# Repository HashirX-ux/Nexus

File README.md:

# Nexus

> A wireless 3x4 macropad i'm building to speed up my workflow. Hot-swap switches, per-key RGB, an OLED screen for status, and a rotary encoder for macros. Works wired or wireless.

---

## What is it?

Nexus is a custom 3x4 (12 key) macropad i designed mainly for shortcuts and repetitive commands i was tired of typing out. Built around a nice!nano v2 so it can do bluetooth LE, with USB-C as a backup if the battery dies or i just don't feel like pairing it again. 12 hot swap sockets, per key RGB underneath, an EC11 rotary encoder, and a little OLED that shows battery % and what its connected to.

(quick note to future me: the tagline used to say QMK somewhere, thats wrong, QMK doesnt really do BLE on this board properly so i switched to ZMK. fix that if you see it anywhere else)

## Why build it

Because reaching over to a full keyboard just to hit a macro or shortcut combo got annoying. If i build the layout, lighting and firmware myself it actually fits how i work instead of some generic layout someone else made.

---

## Status

Research + design phase mostly done, now just cleaning stuff up. Schematic and routing still need some touch ups here and there. Full build log with all the component reasoning is in [journal.md](./journal.md) if you wanna see why i picked what i picked (spoiler: half of it was just "this was in stock on lcsc").

- [x] Component research (MCU, diodes, switches, USB-C, passives)
- [x] Schematic design
- [x] PCB routing
- [x] PCB fabrication
- [x] Firmware pin mapping
- [x] Assembly
- [x] Case design

---

## Planned Specs

| Component | Choice |
|---|---|
| Layout | 3x4, 12 keys |
| MCU | nice!nano v2 (nRF52840) |
| Connectivity | Bluetooth LE (wireless) + USB-C (wired) |
| Switches | Hot-swap, MX-compatible (Kailh / Gateron / Cherry MX) |
| Matrix diodes | 1N4148 |
| RGB | Per-key, WS2812B |
| Encoder | EC11 rotary encoder |
| Display | OLED - battery % + connected device |
| Firmware | ZMK |
| USB | USB-C, USB 2.0 (480Mbps, 5V/500mA) |

---

```
```

Tried to keep this organized roughly the way hack club's [hardware codex shipping guide](https://codex.hackclub.com/shipping/101/) recommends - source files seperate from the manufacturing stuff so its easier for someone else to just grab and rebuild.

> If you dont wanna open kicad just to look at the board, theres a KiCanvas link so you can view it in browser:
> 

---

## Build log

Most of the actual thinking (datasheets i looked at, why i swapped parts, dumb mistakes i made along the way) is in [journal.md](./journal.md). Genuinely recommend reading it if your building something similar, its more useful than just staring at the BOM.

---

## Roadmap

1. finalize schematic (matrix wiring, rgb data line, oled i2c, encoder pins, reset button)
2. route + order the pcb
3. build/test zmk firmware against actual pin assignments (not just what i think they are)
4. design + print the case
5. assemble, flash, pair, hope it works first try

---

## How to build

### 1. order the PCB

1. go to [JLCPCB](https://jlcpcb.com)
2. upload [`Gerber.zip`](./Gerber.zip)
3. settings: 2 layer, FR-4, 1.6mm, HASL (or ENIG if your feeling fancy)
4. order the parts seperately with [`Nexus-BOM.csv`](./Nexus-BOM.csv) as your shopping list - digikey, lcsc, aliexpress all work fine

### 2. print the case

1. open [`cad/`](./cad) - print the `.stl` as is, or crack open the `.f3d` in fusion if you wanna change dimensions
2. 0.2mm layer height, ~20% infill is plenty, its just sitting on a desk not getting thrown around
3. test fit the plate BEFORE you solder anything, learned that one the hard way

### 3. assemble

1. solder the nice!nano v2 diodes resistors and other supprt parts per the [`pcb/`](./pcb) schematic
2. solder in the hot swap sockets, then just press the switches in, no soldering needed there
3. wire the oled, encoder and rgb chain per the pin notes in [`journal.md`](./journal.md)
4. seat the finished pcb intothe case

### 4. flash it

1. follow the zmk build steps in [`firmware/`](./firmware) (shield config + keymap)
2. double tap reset on the nice!nano to drop into UF2 bootloader mode
3. drag the compiled `.uf2` onto the drive that shows up
4. pair over bluetooth, or just plg it in over usb-c if you want wired

### 5. done

flip it over, look at the rgb for a bit, start binding macros. if somethings broken check [`journal.md`](./journal.md) first, saves time vs trying to figure it out from scratch again.

---

## BOM

ful parts list + links in [`Nexus-BOM.csv`](./Nexus-BOM.csv)

---

## Credits

- [ZMK Firmware](https://zmk.dev/)
- [nice!nano](https://nicekeyboards.com/nice-nano/)
- [nice!nano docs](https://nicekeyboards.com/docs/nice-nano/) - pinout + hardware ref, used this constantly

Built by **Hashir**

---

## License

MIT, see [LICENSE](./LICENSE)

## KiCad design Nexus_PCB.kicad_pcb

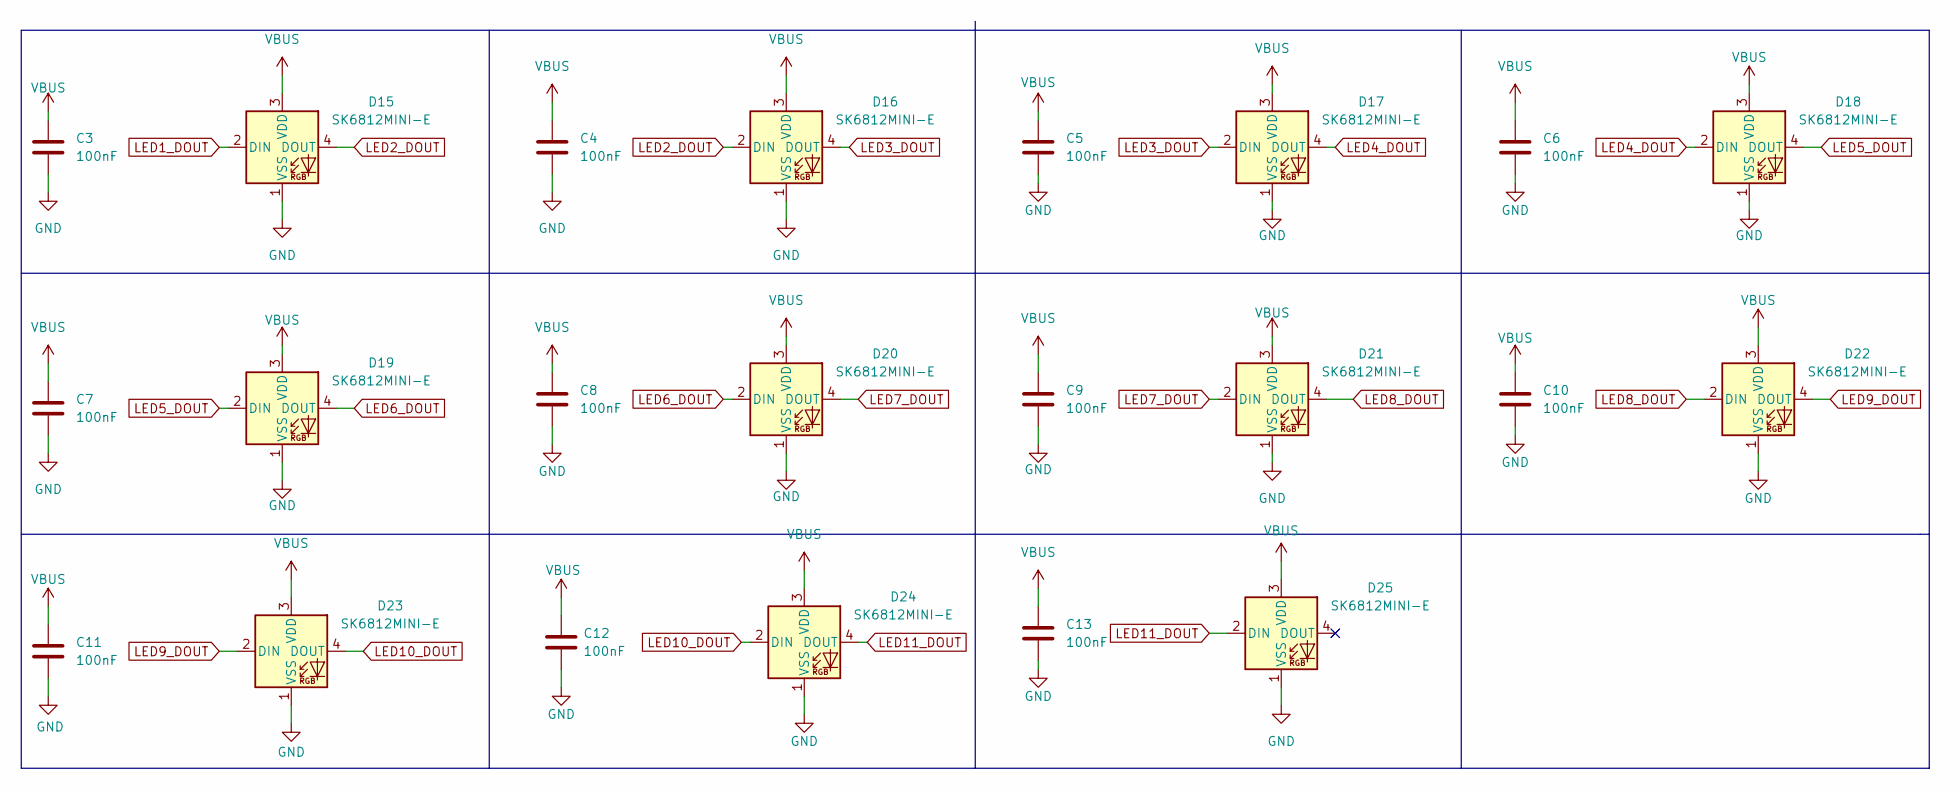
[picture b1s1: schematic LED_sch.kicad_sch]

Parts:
C3, C4, C5, C6, C7, C8, C9, C10, C11, C12, C13: 100nF; C_0805_2012Metric_Pad1.18x1.45mm_HandSolder
D15, D16, D17, D18, D19, D20, D21, D22, D23, D24, D25: SK6812MINI-E; LED_SK6812MINI-E_3.2x2.8mm_P1.5mm_ReverseMount

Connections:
GND: C3.2, C4.2, C5.2, C6.2, C7.2, C8.2, C9.2, C10.2, C11.2, C12.2, C13.2, D15.1 (VSS), D16.1 (VSS), D17.1 (VSS), D18.1 (VSS), D19.1 (VSS), D20.1 (VSS), D21.1 (VSS), D22.1 (VSS), D23.1 (VSS), D24.1 (VSS), D25.1 (VSS); also elsewhere on the board
LED1_DOUT: D15.2 (DIN); also elsewhere on the board
LED2_DOUT: D15.4 (DOUT), D16.2 (DIN)
LED3_DOUT: D16.4 (DOUT), D17.2 (DIN)
LED4_DOUT: D17.4 (DOUT), D18.2 (DIN)
LED5_DOUT: D18.4 (DOUT), D19.2 (DIN)
LED6_DOUT: D19.4 (DOUT), D20.2 (DIN)
LED7_DOUT: D20.4 (DOUT), D21.2 (DIN)
LED8_DOUT: D21.4 (DOUT), D22.2 (DIN)
LED9_DOUT: D22.4 (DOUT), D23.2 (DIN)
LED10_DOUT: D23.4 (DOUT), D24.2 (DIN)
LED11_DOUT: D24.4 (DOUT), D25.2 (DIN)
VBUS: C3.1, C4.1, C5.1, C6.1, C7.1, C8.1, C9.1, C10.1, C11.1, C12.1, C13.1, D15.3 (VDD), D16.3 (VDD), D17.3 (VDD), D18.3 (VDD), D19.3 (VDD), D20.3 (VDD), D21.3 (VDD), D22.3 (VDD), D23.3 (VDD), D24.3 (VDD), D25.3 (VDD); also elsewhere on the board

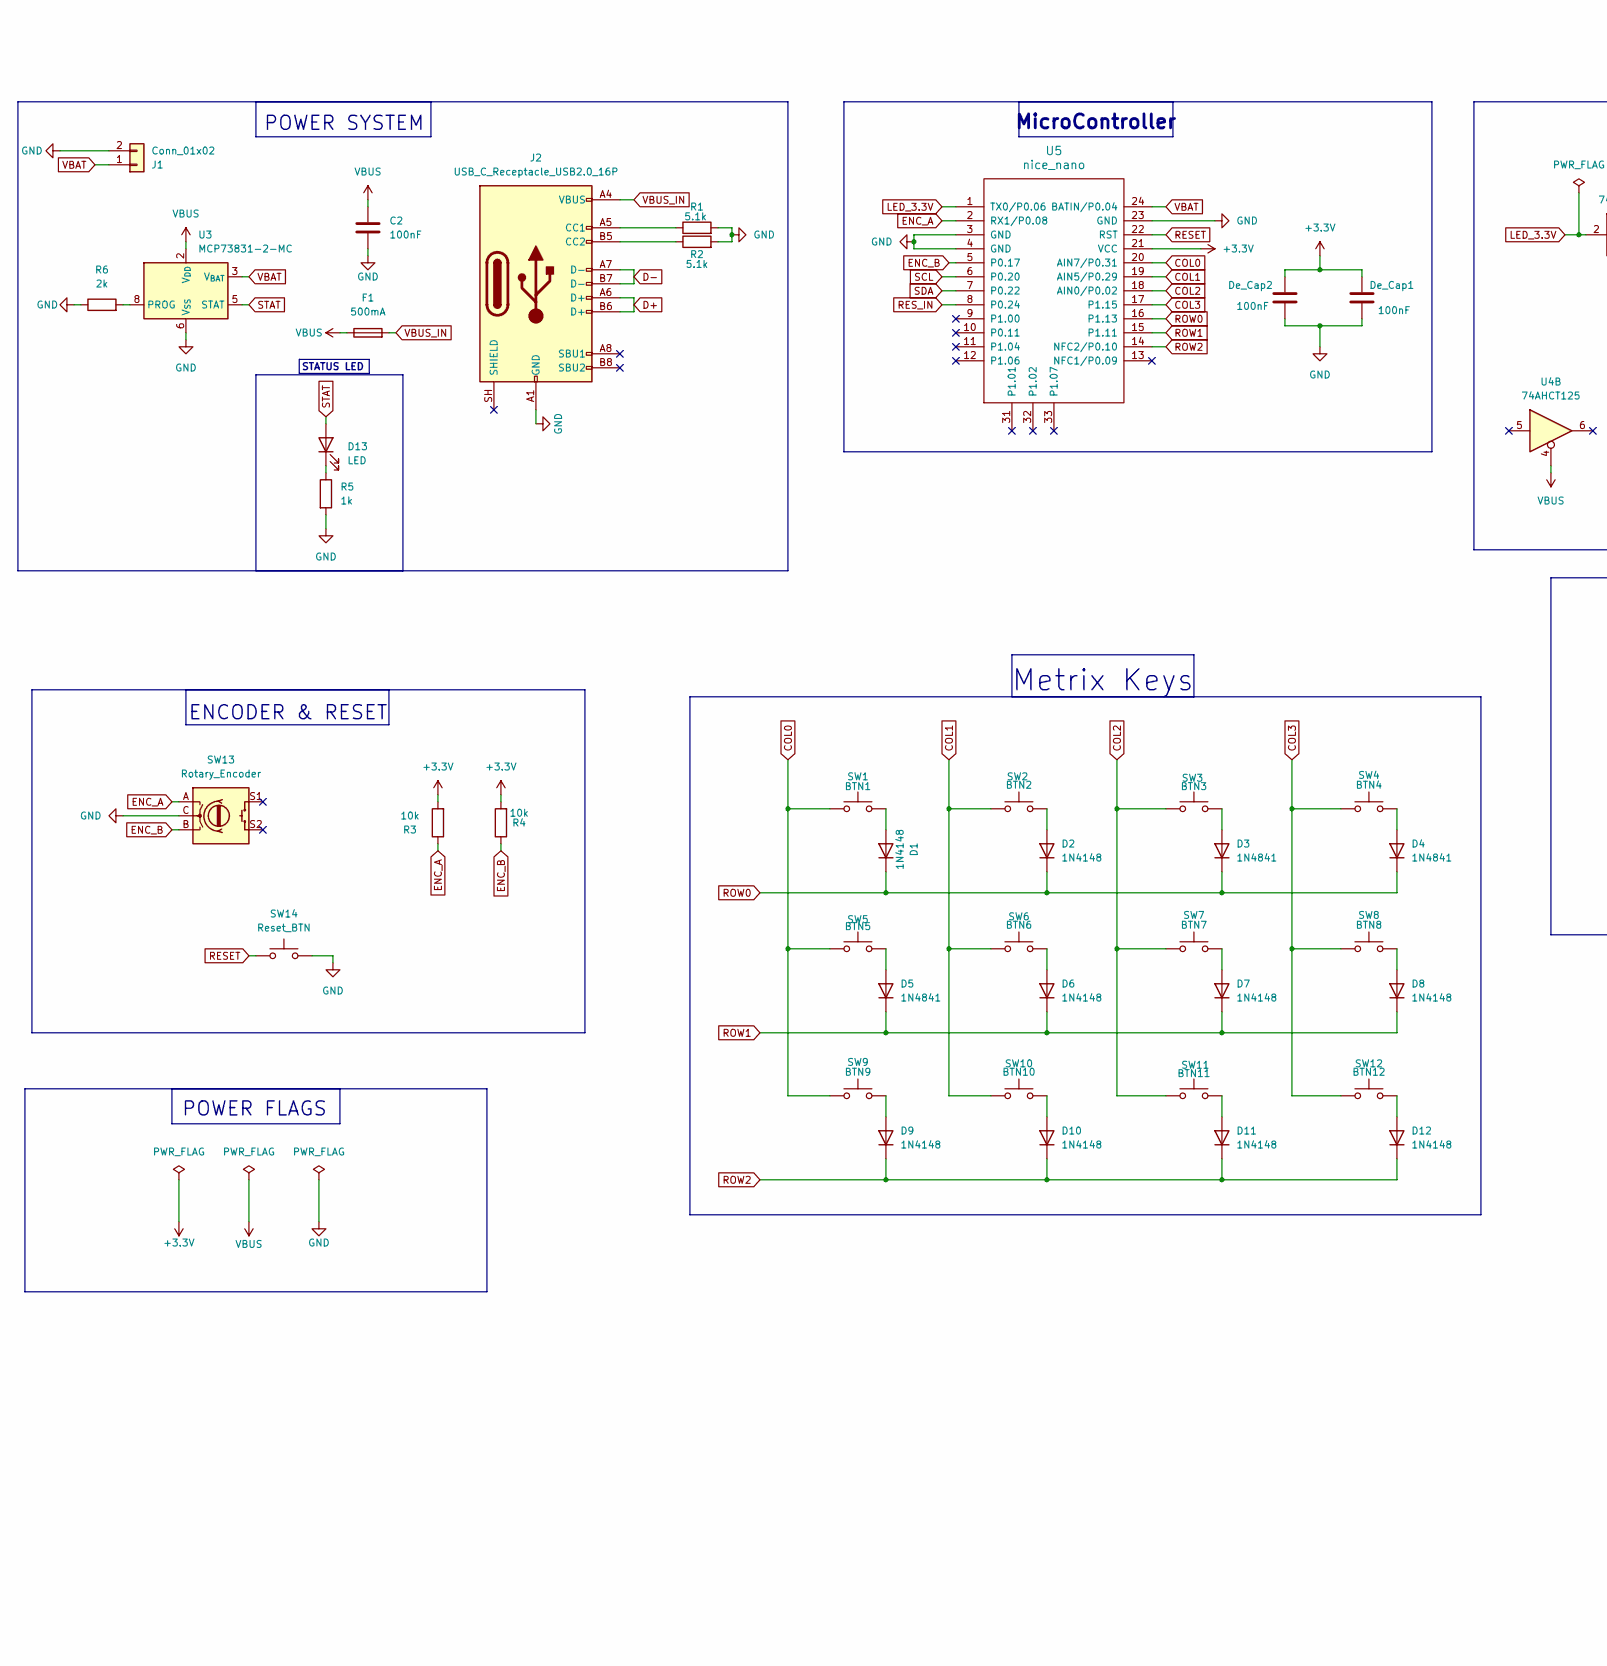
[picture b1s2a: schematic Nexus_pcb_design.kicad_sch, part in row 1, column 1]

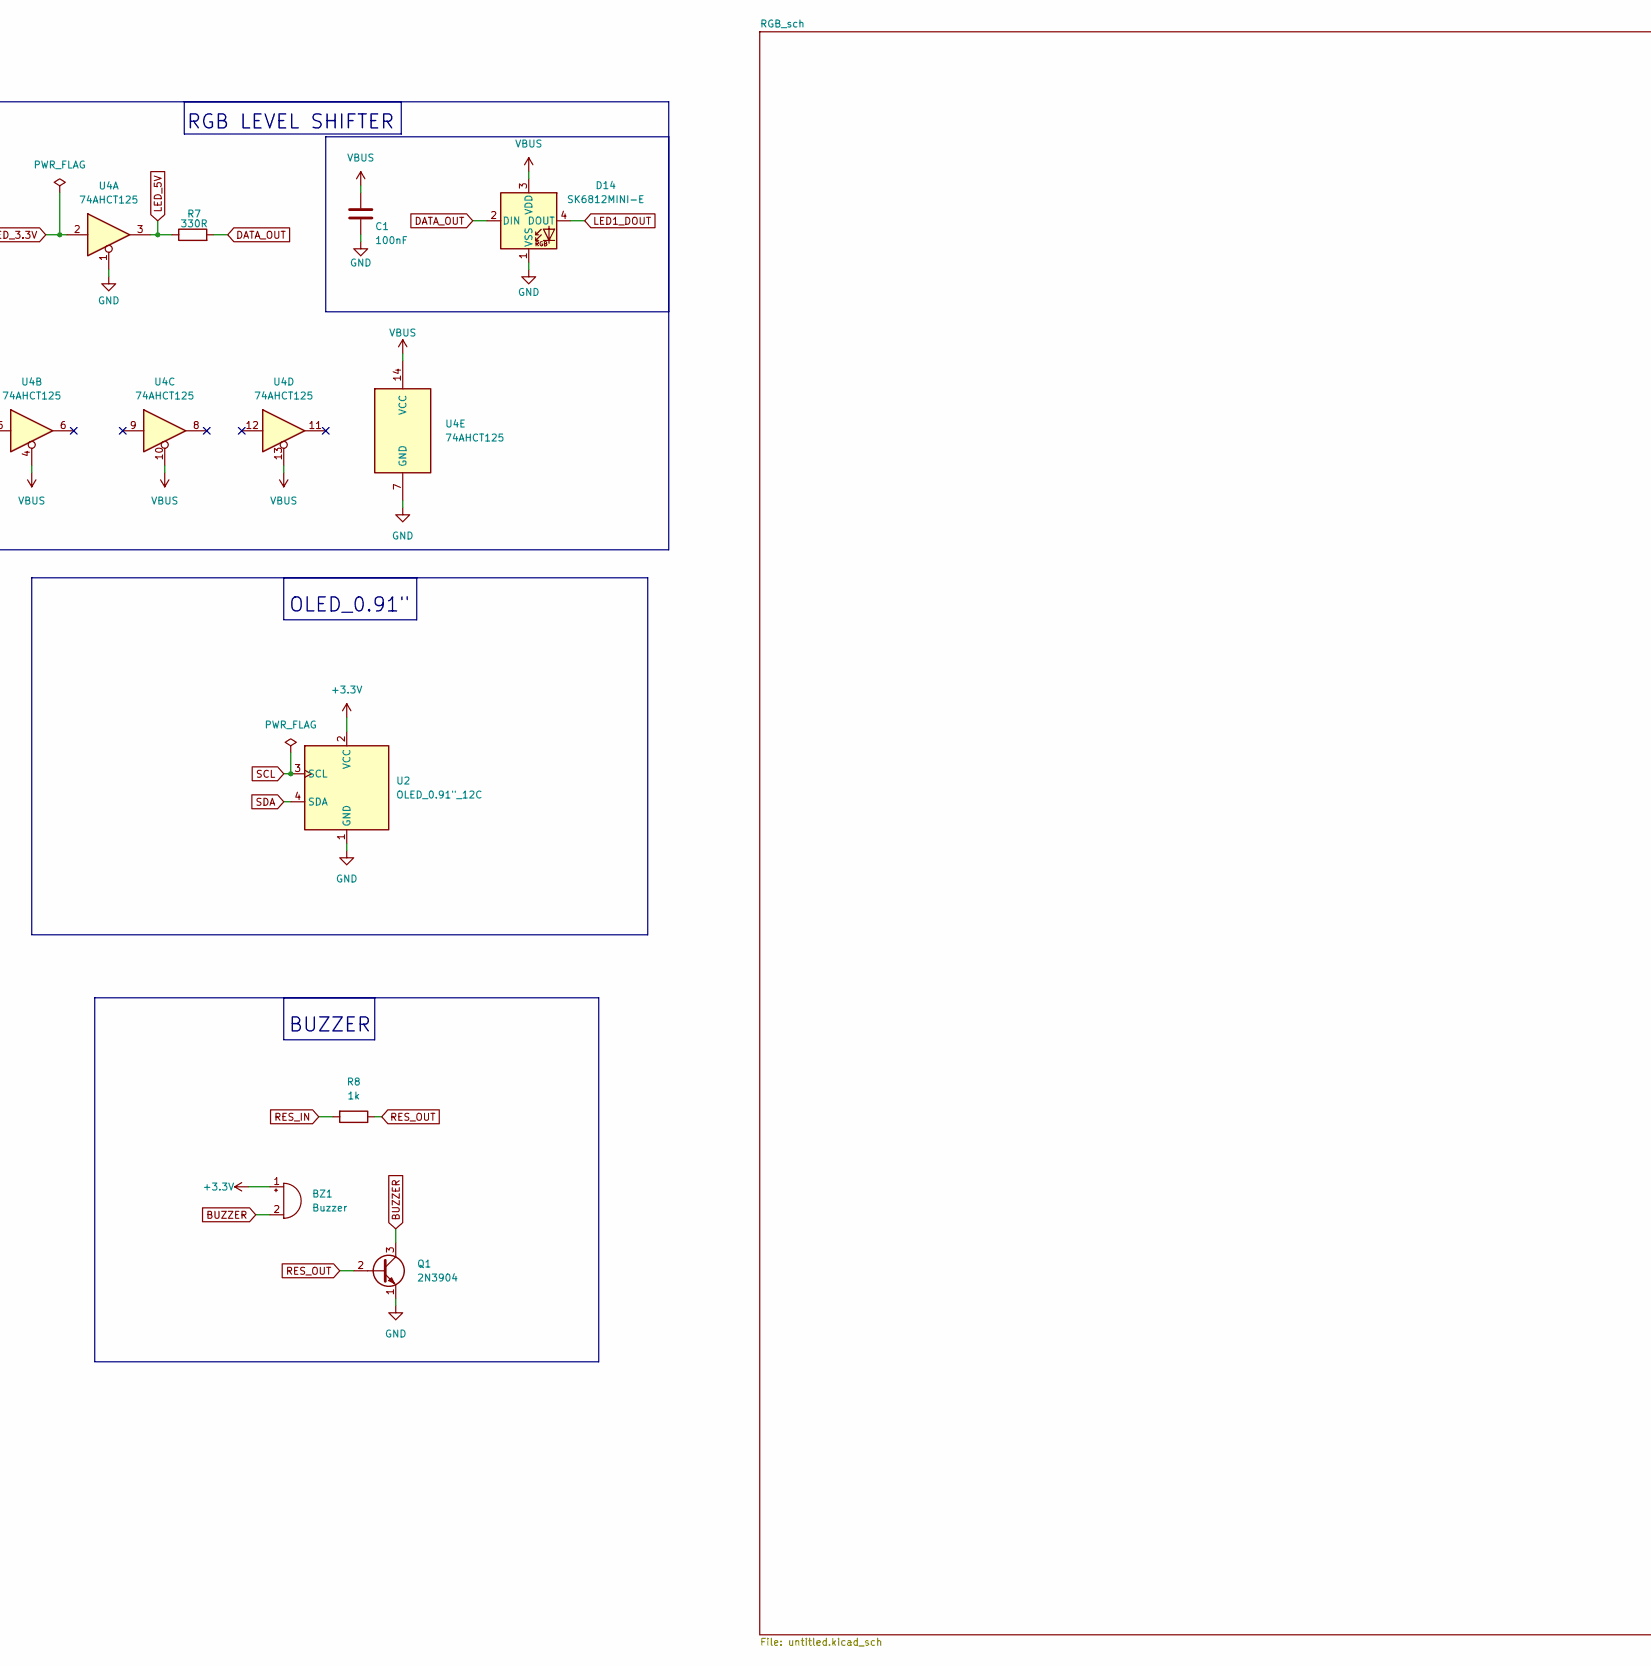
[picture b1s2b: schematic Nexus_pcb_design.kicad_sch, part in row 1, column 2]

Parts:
BZ1: Buzzer; Buzzer_12x9.5RM7.6
C1, C2: 100nF; C_0805_2012Metric_Pad1.18x1.45mm_HandSolder
D1, D2, D6, D7, D8, D9, D10, D11, D12: 1N4148; D_SOD-123
D3, D4, D5: 1N4841; D_SOD-123
D13: LED; LED_0603_1608Metric
D14: SK6812MINI-E; LED_SK6812MINI-E_3.2x2.8mm_P1.5mm_ReverseMount
De_Cap1, De_Cap2: 100nF; C_0805_2012Metric_Pad1.18x1.45mm_HandSolder
F1: 500mA; Fuse_1206_3216Metric
J1: Conn_01x02; JST_PH_B2B-PH-K_1x02_P2.00mm_Vertical
J2: USB_C_Receptacle_USB2.0_16P; USB_C_Receptacle_GCT_USB4105-xx-A_16P_TopMnt_Horizontal
Q1: 2N3904; TO-92_Inline
R1, R2: 5.1k; R_0603_1608Metric_Pad0.98x0.95mm_HandSolder
R3, R4: 10k; R_0603_1608Metric_Pad0.98x0.95mm_HandSolder
R5: 1k; R_1206_3216Metric
R6: 2k; R_0603_1608Metric_Pad0.98x0.95mm_HandSolder
R7: 330R; R_0603_1608Metric_Pad0.98x0.95mm_HandSolder
R8: 1k; R_0805_2012Metric
SW1: BTN1; SW_Hotswap_Kailh_MX_1.00u
SW2: BTN2; SW_Hotswap_Kailh_MX_1.00u
SW3: BTN3; SW_Hotswap_Kailh_MX_1.00u
SW4: BTN4; SW_Hotswap_Kailh_MX_1.00u
SW5: BTN5; SW_Hotswap_Kailh_MX_1.00u
SW6: BTN6; SW_Hotswap_Kailh_MX_1.00u
SW7: BTN7; SW_Hotswap_Kailh_MX_1.00u
SW8: BTN8; SW_Hotswap_Kailh_MX_1.00u
SW9: BTN9; SW_Hotswap_Kailh_MX_1.00u
SW10: BTN10; SW_Hotswap_Kailh_MX_1.00u
SW11: BTN11; SW_Hotswap_Kailh_MX_1.00u
SW12: BTN12; SW_Hotswap_Kailh_MX_1.00u
SW13: Rotary_Encoder; RotaryEncoder_Alps_EC11E-Switch_Vertical_H20mm_MountingHoles
SW14: Reset_BTN; SW_Push_1P1T_NO_CK_KMR2
U2: OLED_0.91"_12C; ER_OLEDM0.91_1x-I2C
U3: MCP73831-2-MC; DFN-8-1EP_3x2mm_P0.5mm_EP1.7x1.4mm
U4: 74AHCT125; TSSOP-14_4.4x5mm_P0.65mm
U5: nice_nano

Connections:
+3.3V: BZ1.1 (+), De_Cap1.1, De_Cap2.1, R3.2, R4.2, U2.2 (VCC), U5.21 (VCC)
BUZZER: BZ1.2 (-), Q1.3 (C)
COL0: SW1.1, SW5.1, SW9.1, U5.20 (AIN7/P0.31)
COL1: SW2.1, SW6.1, SW10.1, U5.19 (AIN5/P0.29)
COL2: SW3.1, SW7.1, SW11.1, U5.18 (AIN0/P0.02)
COL3: SW4.1, SW8.1, SW12.1, U5.17 (P1.15)
D+: J2.A6 (D+), J2.B6 (D+)
D-: J2.A7 (D-), J2.B7 (D-)
DATA_OUT: D14.2 (DIN), R7.2
ENC_A: R3.1, SW13.A, U5.2 (RX1/P0.08)
ENC_B: R4.1, SW13.B, U5.5 (P0.17)
GND: C1.2, C2.2, D14.1 (VSS), De_Cap1.2, De_Cap2.2, J1.2, J2.A1 (GND), J2.A12 (GND), J2.B1 (GND), J2.B12 (GND), Q1.1 (E), R1.2, R2.2, R5.2, R6.1, SW13.C, SW14.2, U2.1 (GND), U3.6 (V_{SS}), U4.1, U4.7 (GND), U5.3 (GND), U5.4 (GND), U5.23 (GND); also elsewhere on the board
LED1_DOUT: D14.4 (DOUT); also elsewhere on the board
LED_3.3V: U4.2, U5.1 (TX0/P0.06)
LED_5V: R7.1, U4.3
unnamed: D1.2 (A), SW1.2
unnamed: D2.2 (A), SW2.2
unnamed: D3.2 (A), SW3.2
unnamed: D4.2 (A), SW4.2
unnamed: D5.2 (A), SW5.2
unnamed: D6.2 (A), SW6.2
unnamed: D7.2 (A), SW7.2
unnamed: D8.2 (A), SW8.2
unnamed: D9.2 (A), SW9.2
unnamed: D10.2 (A), SW10.2
unnamed: D11.2 (A), SW11.2
unnamed: D12.2 (A), SW12.2
unnamed: D13.1 (K), R5.1
unnamed: J2.A5 (CC1), R1.1
unnamed: J2.B5 (CC2), R2.1
unnamed: R6.2, U3.8 (PROG)
RESET: SW14.1, U5.22 (RST)
RES_IN: R8.2, U5.8 (P0.24)
RES_OUT: Q1.2 (B), R8.1
ROW0: D1.1 (K), D2.1 (K), D3.1 (K), D4.1 (K), U5.16 (P1.13)
ROW1: D5.1 (K), D6.1 (K), D7.1 (K), D8.1 (K), U5.15 (P1.11)
ROW2: D9.1 (K), D10.1 (K), D11.1 (K), D12.1 (K), U5.14 (NFC2/P0.10)
SCL: U2.3 (SCL), U5.6 (P0.20)
SDA: U2.4 (SDA), U5.7 (P0.22)
STAT: D13.2 (A), U3.5 (STAT)
VBAT: J1.1, U3.3 (V_{BAT}), U3.4 (V_{BAT}), U5.24 (BATIN/P0.04)
VBUS: C1.1, C2.1, D14.3 (VDD), F1.1, U3.1 (V_{DD}), U3.2 (V_{DD}), U4.4, U4.10, U4.13, U4.14 (VCC); also elsewhere on the board
VBUS_IN: F1.2, J2.A4 (VBUS), J2.A9 (VBUS), J2.B4 (VBUS), J2.B9 (VBUS)

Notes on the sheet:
STATUS LED
BUZZER
ENCODER & RESET
POWER FLAGS
Metrix Keys
POWER SYSTEM
RGB LEVEL SHIFTER
OLED_0.91"
MicroController

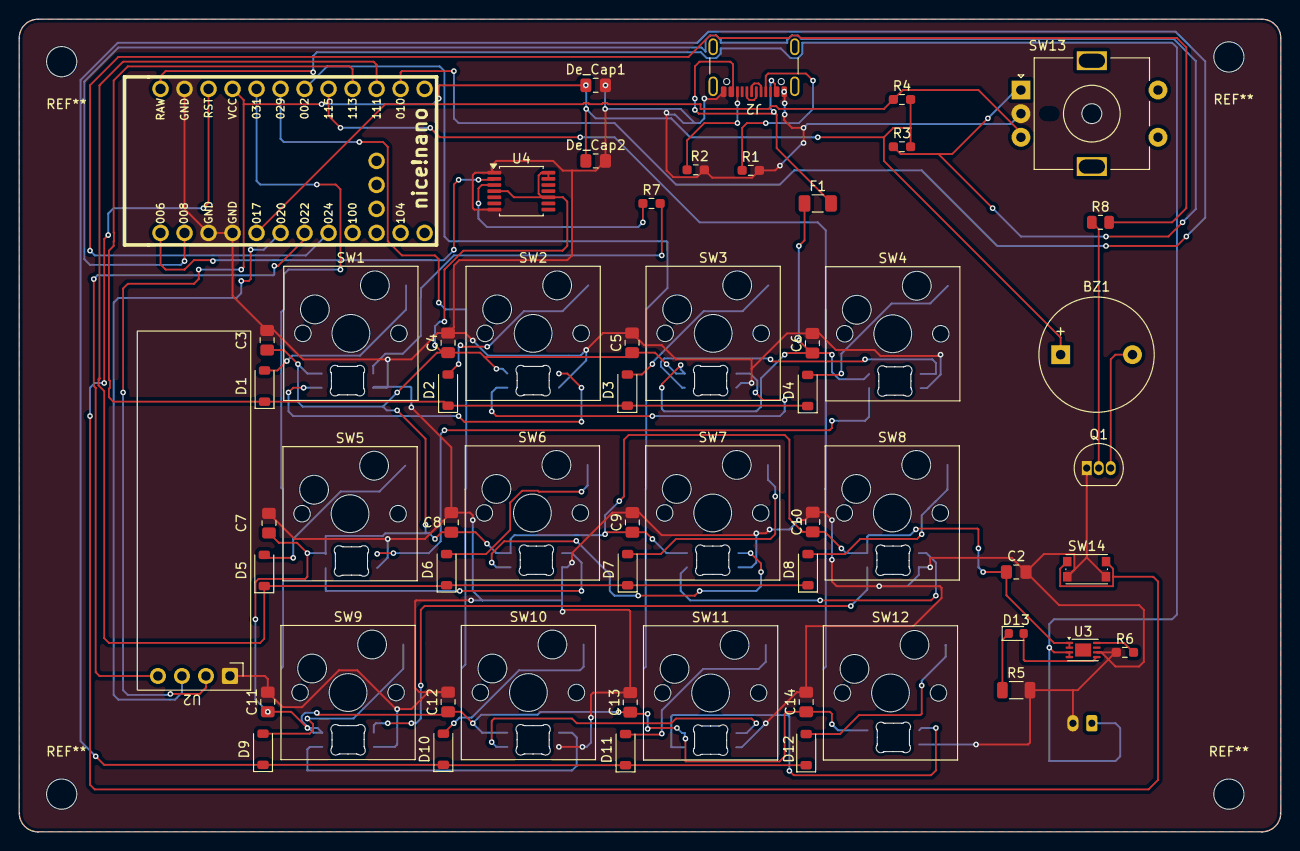
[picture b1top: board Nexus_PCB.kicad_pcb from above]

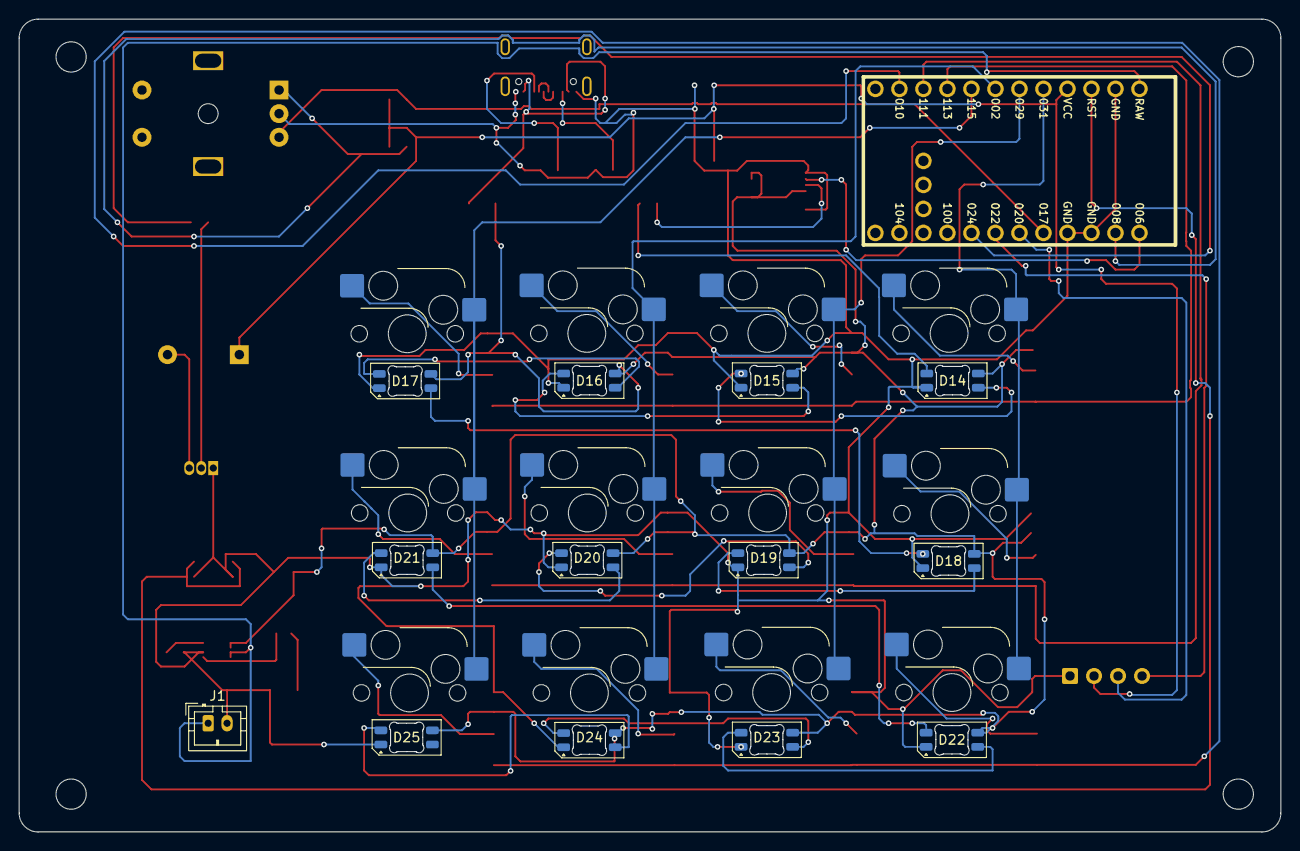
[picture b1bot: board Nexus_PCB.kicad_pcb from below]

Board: 2 copper layers, 133.5 x 86.0 mm, 71 parts (13 on the bottom side), 53 nets.

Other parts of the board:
C14: 100nF; C_0805_2012Metric_Pad1.18x1.45mm_HandSolder

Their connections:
GND: C14.2; also elsewhere on the board
VBUS: C14.1; also elsewhere on the board
